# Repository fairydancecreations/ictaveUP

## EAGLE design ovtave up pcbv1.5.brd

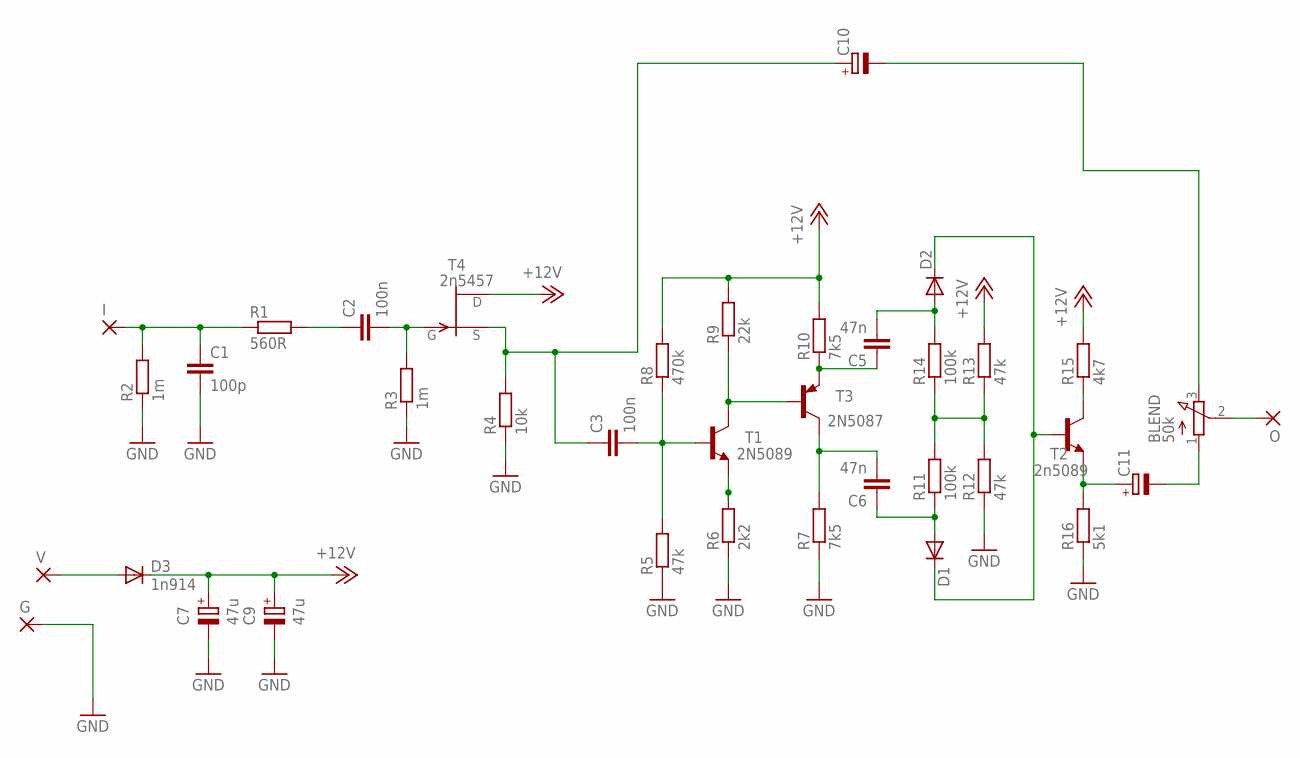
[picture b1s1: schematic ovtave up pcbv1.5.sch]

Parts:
BLEND: 50k; 3RP/1610N
C1: 100p; C5B2.5
C2, C3: 100n; C5B2.5
C5, C6: 47n; C5B2.5
C7, C9: 47u; E2-4
C10, C11: CPOL-EUE2-4; E2-4
D1, D2: Ge fV match; DO35-7
D3: 1n914; DO35-7
G: 1,6/0,9
I: 1,6/0,9
O: 1,6/0,9
R1: 560R; 0207/7
R2, R3: 1m; 0207/7
R4: 10k; 0207/7
R5, R12, R13: 47k; 0207/7
R6: 2k2; 0207/7
R7, R10: 7k5; 0207/7
R8: 470k; 0207/7
R9: 22k; 0207/7
R11, R14: 100k; 0207/7
R15: 4k7; 0207/7
R16: 5k1; 0207/7
T1: 2N5089; TO92
T2: 2n5089; TO92
T3: 2N5087; TO92
T4: 2n5457; TO92
V: 1,6/0,9

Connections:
+12V: C7.+, C9.+, D3.C, R8.2, R9.2, R10.2, R13.2, R15.2, T4.3 (D)
GND: C1.2, C7.-, C9.-, G.1, R2.1, R3.1, R4.1, R5.1, R6.1, R7.1, R12.1, R16.1
unnamed: C1.1, I.1, R1.1, R2.2
unnamed: C2.2, R3.2, T4.1 (G)
unnamed: C2.1, R1.2
unnamed: BLEND.3 (E), C10.-
unnamed: R9.1, T1.1 (C), T3.2 (B)
unnamed: R6.2, T1.3 (E)
unnamed: BLEND.1 (A), C11.-
unnamed: C3.2, R5.2, R8.1, T1.2 (B)
unnamed: R15.1, T2.1 (C)
unnamed: C6.2, R7.2, T3.1 (C)
unnamed: R11.2, R12.2, R13.1, R14.1
unnamed: C3.1, C10.+, R4.2, T4.2 (S)
unnamed: C6.1, D1.A, R11.1
unnamed: D3.A, V.1
unnamed: D1.C, D2.C, T2.2 (B)
unnamed: C5.2, D2.A, R14.2
unnamed: C11.+, R16.2, T2.3 (E)
unnamed: BLEND.2 (S), O.1
unnamed: C5.1, R10.1, T3.3 (E)

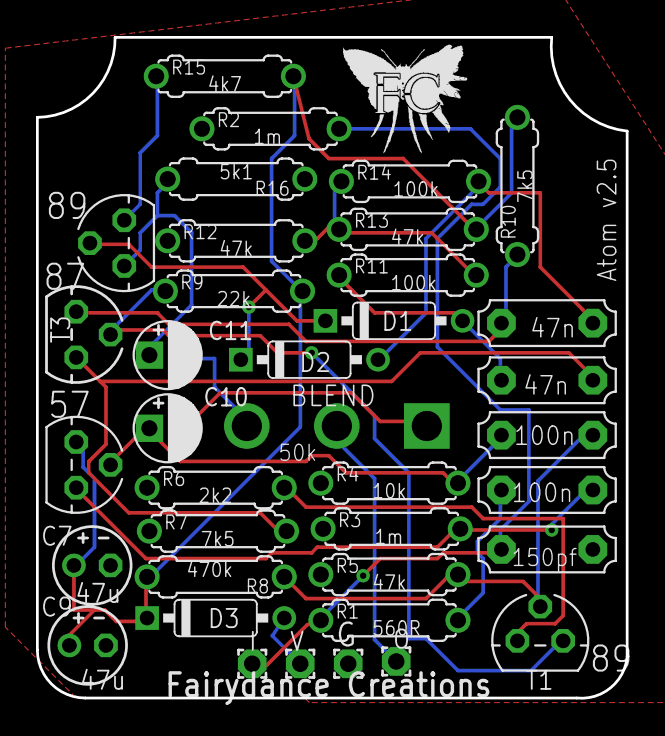
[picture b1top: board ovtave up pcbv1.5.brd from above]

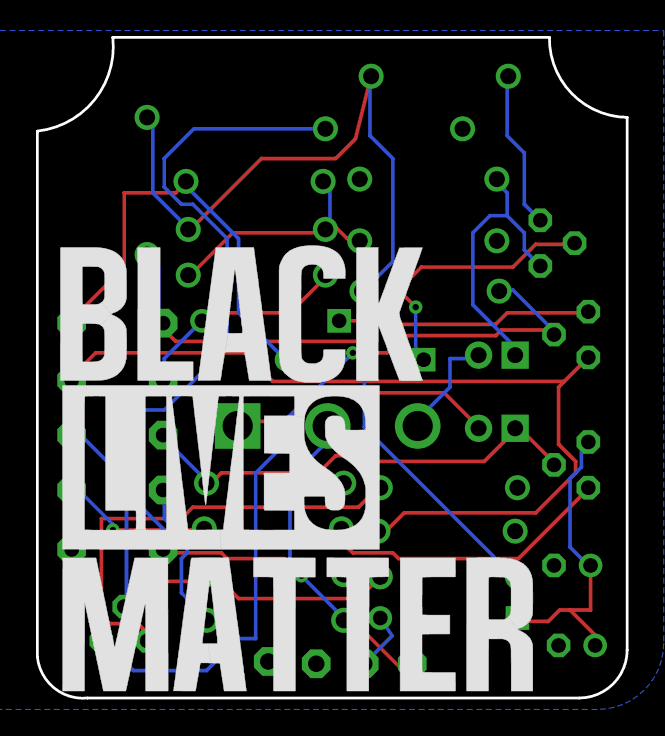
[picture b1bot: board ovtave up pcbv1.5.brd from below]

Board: 2 copper layers, 32.8 x 36.7 mm, 40 parts (3 on the bottom side), 21 nets.

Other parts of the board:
U$1: BLACK-SILK-MD
U$2: LIVES-SILK-MD
U$3: MATTER-SILK-MD

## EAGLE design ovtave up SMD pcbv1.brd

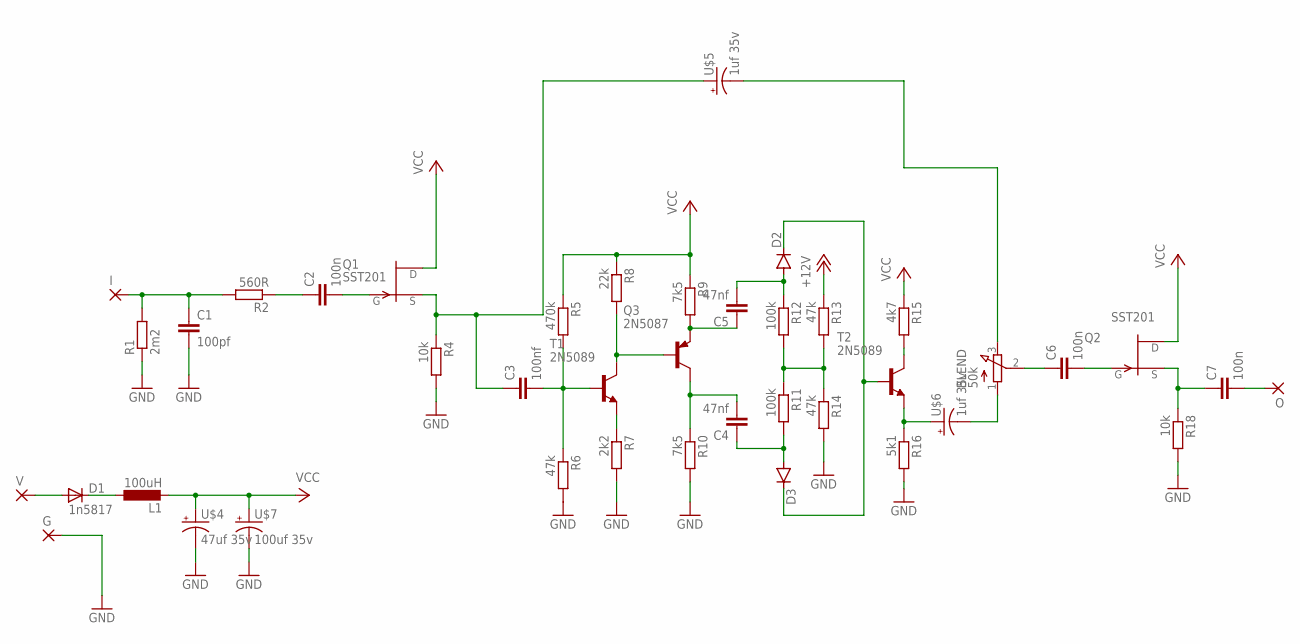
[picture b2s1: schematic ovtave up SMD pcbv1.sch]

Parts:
BLEND: 50k; 3RP/1610N
C1: 100pf; C0805K
C2, C6, C7: 100n; C0805K
C3: 100nf; C0805K
C4, C5: 47nf; C0805K
D1: 1n5817; DO35-7
D2, D3: AA112; DO07
G: 1,6/0,9
I: 1,6/0,9
L1: 100uH; L2012C
O: 1,6/0,9
Q1, Q2: SST201; SOT23
Q3: 2N5087; TO92
R1: 2m2; M0805
R2: 560R; M0805
R4, R18: 10k; M0805
R5: 470k; M0805
R6, R13, R14: 47k; M0805
R7: 2k2; M0805
R8: 22k; M0805
R9, R10: 7k5; M0805
R11, R12: 100k; M0805
R15: 4k7; M0805
R16: 5k1; M0805
T1, T2: 2N5089; TO92
U$4: 47uf 35v; PAN_B_SMD+THRU
U$5, U$6: 1uf 35v; PAN_B_SMD+THRU
U$7: 100uf 35v; PAN_C_SMD+THRU
V: 1,6/0,9

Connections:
+12V: R13.1
GND: C1.2, G.1, R1.1, R4.2, R6.2, R7.2, R10.2, R14.2, R16.2, R18.2, U$4.-, U$4.-- (-), U$7.-, U$7.-- (-)
unnamed: C1.1, I.1, R1.2, R2.2
unnamed: C2.2, Q1.3 (G)
unnamed: C2.1, R2.1
unnamed: BLEND.3 (E), U$5.-, U$5.-- (-)
unnamed: D1.C, L1.1
unnamed: Q3.2 (B), R8.2, T1.1 (C)
unnamed: C6.2, Q2.3 (G)
unnamed: BLEND.1 (A), U$6.-, U$6.-- (-)
unnamed: C3.2, R5.2, R6.1, T1.2 (B)
unnamed: R15.2, T2.1 (C)
unnamed: C4.2, Q3.1 (C), R10.1
unnamed: R7.1, T1.3 (E)
unnamed: R11.1, R12.2, R13.2, R14.1
unnamed: C3.1, Q1.2 (S), R4.1, U$5.+, U$5.++ (+)
unnamed: C4.1, D3.A, R11.2
unnamed: D1.A, V.1
unnamed: D2.C, D3.C, T2.2 (B)
unnamed: C5.2, D2.A, R12.1
unnamed: R16.1, T2.3 (E), U$6.+, U$6.++ (+)
unnamed: C7.1, Q2.2 (S), R18.1
unnamed: C7.2, O.1
unnamed: BLEND.2 (S), C6.1
unnamed: C5.1, Q3.3 (E), R9.2
VCC: L1.2, Q1.1 (D), Q2.1 (D), R5.1, R8.1, R9.1, R15.1, U$4.+, U$4.++ (+), U$7.+, U$7.++ (+)

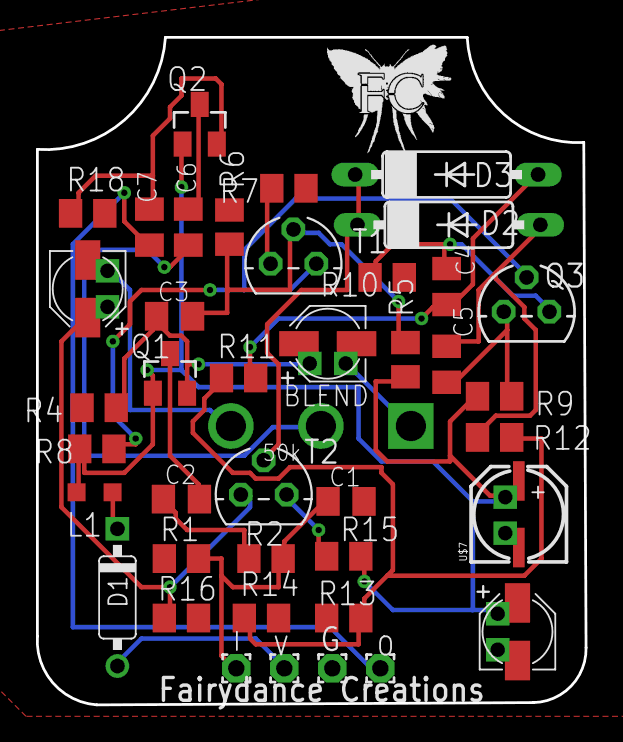
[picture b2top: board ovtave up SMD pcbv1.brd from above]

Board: 2 copper layers, 30.5 x 37.1 mm, 41 parts (0 on the bottom side), 25 nets.
